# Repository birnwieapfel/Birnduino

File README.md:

# birnduino
An Arduino clone with an RS232 serial interface.

In 2013, I bought a board call "Freeduino Serial v2.0", which is an Arduino clone having an RS232 serial interface using a MAX232. But it seems that it is not available anymore now and I could not find the original files of the "v2.0". So I decided to create my own based on some information about the Freeduino I found in the internet and having a look at my "Freeduino Serial v2.0" board...

## Repository content
- The [inputs folder](inputs) contains the resources which helped me to create the schematic and PCB
- The [datasheets folder](datasheets) contains the datasheets for the used ICs
- The KiCad 6.0 files for the schematic and PCB are in the [KiCad subfolder](KiCad)
- *to come...* Image(s) of the PCB can be found in the folder *images*

## Old resouces
Here are some links which helped to realize this project:
- https://thdarduino.blogspot.com/2015/12/freeduino-serial-v20-bausatz.html

## Other links
- https://freeduino.org/freeduino_open_designs-html
- https://github.com/WestfW/Freeduino-historical

## License
Copyright 2022, Robert Birn. All Rights Reserved.

"birnduino" is licensed under [CC BY-SA 4.0](https://creativecommons.org/licenses/by-sa/4.0/legalcode) by Robert Birn.

This work, "birnduino", is a derivative of "Freeduino Serial" by CircuitJoy and Spiffed, released under CC BY-SA 2.5. 

"Freeduino Serial" is based on the Arduino Diecimila reference design (www.arduino.cc/main/ArduinoBoardDiecimila).

I started the work by using the **Arduino KiCad Library**, available here: https://github.com/Alarm-Siren/arduino-kicad-library. Remark: After an update, no reference to this library is existing anymore.

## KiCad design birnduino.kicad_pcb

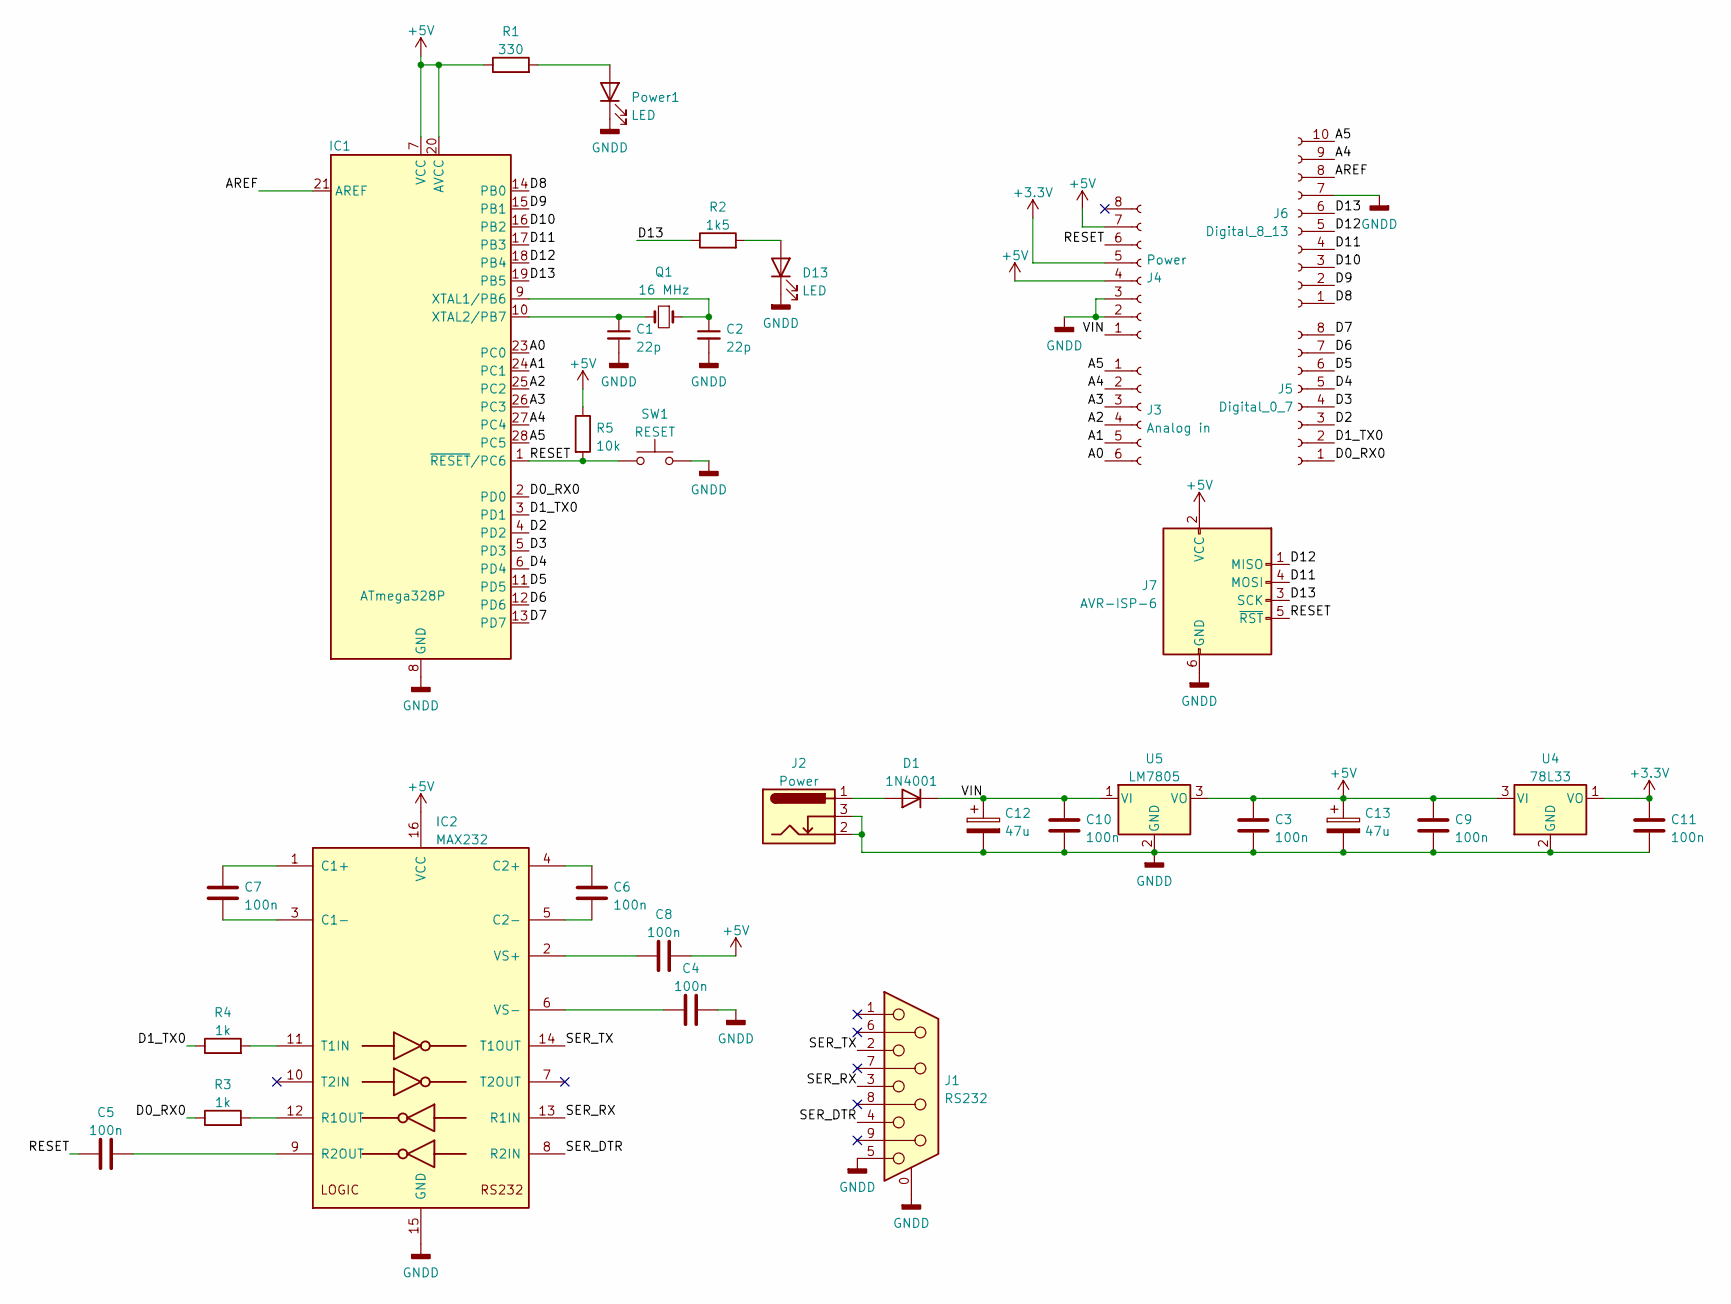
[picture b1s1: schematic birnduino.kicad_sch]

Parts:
C1, C2: 22p; C_Rect_L7.0mm_W2.0mm_P5.00mm
C3, C4, C5, C6, C7, C8, C9, C10, C11: 100n; C_Rect_L7.0mm_W2.0mm_P5.00mm
C12, C13: 47u; CP_Radial_D6.3mm_P2.50mm
D1: 1N4001; D_DO-41_SOD81_P10.16mm_Horizontal
D13: LED; LED_D3.0mm
IC1: ATmega328P; DIP-28_W7.62mm
IC2: MAX232; DIP-16_W7.62mm
J1: RS232; DSUB-9_Female_Horizontal_P2.77x2.84mm_EdgePinOffset7.70mm_H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
J2: Power; BarrelJack_Horizontal
J3: Analog in; PinSocket_1x06_P2.54mm_Vertical
J4: Power; PinSocket_1x08_P2.54mm_Vertical
J5: Digital_0_7; PinSocket_1x08_P2.54mm_Vertical
J6: Digital_8_13; PinSocket_1x10_P2.54mm_Vertical
J7: AVR-ISP-6; PinHeader_2x03_P2.54mm_Vertical
Power1: LED; LED_D3.0mm
Q1: 16 MHz; Crystal_HC49-U_Vertical
R1: 330; R_Axial_DIN0207_L6.3mm_D2.5mm_P10.16mm_Horizontal
R2: 1k5; R_Axial_DIN0207_L6.3mm_D2.5mm_P10.16mm_Horizontal
R3, R4: 1k; R_Axial_DIN0207_L6.3mm_D2.5mm_P10.16mm_Horizontal
R5: 10k; R_Axial_DIN0207_L6.3mm_D2.5mm_P10.16mm_Horizontal
SW1: RESET; SW_PUSH_6mm
U4: 78L33; TO-92_Inline
U5: LM7805; TO-220-3_Vertical

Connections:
+3V3: C11.1, J4.5, U4.1 (VO)
+5V: C3.1, C8.1, C9.1, C13.1, IC1.7 (VCC), IC1.20 (AVCC), IC2.16 (VCC), J4.4, J4.7, J7.2 (VCC), R1.1, R5.1, U4.3 (VI), U5.3 (VO)
/A0: IC1.23 (PC0), J3.6
/A1: IC1.24 (PC1), J3.5
/A2: IC1.25 (PC2), J3.4
/A3: IC1.26 (PC3), J3.3
/A4: IC1.27 (PC4), J3.2, J6.9
/A5: IC1.28 (PC5), J3.1, J6.10
/AREF: IC1.21 (AREF), J6.8
/D0_RX0: IC1.2 (PD0), J5.1, R3.1
/D1_TX0: IC1.3 (PD1), J5.2, R4.1
/D2: IC1.4 (PD2), J5.3
/D3: IC1.5 (PD3), J5.4
/D4: IC1.6 (PD4), J5.5
/D5: IC1.11 (PD5), J5.6
/D6: IC1.12 (PD6), J5.7
/D7: IC1.13 (PD7), J5.8
/D8: IC1.14 (PB0), J6.1
/D9: IC1.15 (PB1), J6.2
/D10: IC1.16 (PB2), J6.3
/D11: IC1.17 (PB3), J6.4, J7.4 (MOSI)
/D12: IC1.18 (PB4), J6.5, J7.1 (MISO)
/D13: IC1.19 (PB5), J6.6, J7.3 (SCK), R2.1
/RESET: C5.2, IC1.1 (~RESET/PC6), J4.6, J7.5 (~RST), R5.2, SW1.1
/SER_DTR: IC2.8 (R2IN), J1.4
/SER_RX: IC2.13 (R1IN), J1.3
/SER_TX: IC2.14 (T1OUT), J1.2
/VIN: C10.1, C12.1, D1.1 (K), J4.1, U5.1 (VI)
GNDD: C1.2, C2.2, C3.2, C4.2, C9.2, C10.2, C11.2, C12.2, C13.2, D13.1 (K), IC1.8 (GND), IC1.22 (GND), IC2.15 (GND), J1.0 (PAD), J1.5, J2.2, J2.3, J4.2, J4.3, J6.7, J7.6 (GND), Power1.1 (K), SW1.2, U4.2 (GND), U5.2 (GND)
unnamed: C1.1, IC1.10 (XTAL2/PB7), Q1.2
unnamed: C2.1, IC1.9 (XTAL1/PB6), Q1.1
unnamed: C4.1, IC2.6 (VS-)
unnamed: C5.1, IC2.9 (R2OUT)
unnamed: C6.1, IC2.4 (C2+)
unnamed: C6.2, IC2.5 (C2-)
unnamed: C7.1, IC2.1 (C1+)
unnamed: C7.2, IC2.3 (C1-)
unnamed: C8.2, IC2.2 (VS+)
unnamed: D1.2 (A), J2.1
unnamed: D13.2 (A), R2.2
unnamed: IC2.11 (T1IN), R4.2
unnamed: IC2.12 (R1OUT), R3.2
unnamed: Power1.2 (A), R1.2

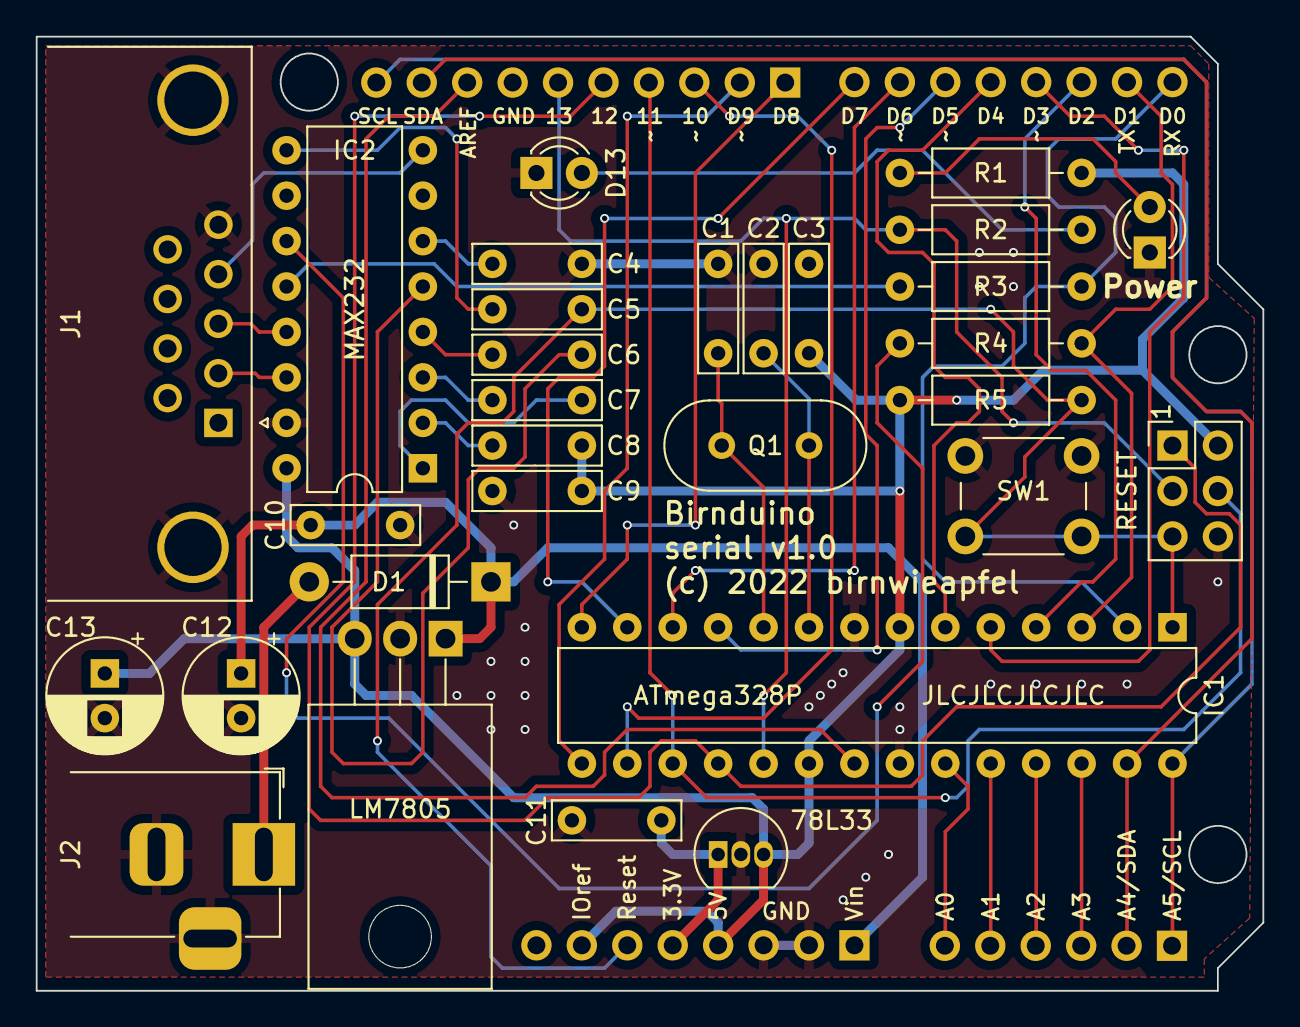
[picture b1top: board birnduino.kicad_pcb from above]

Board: 2 copper layers, 68.6 x 53.3 mm, 34 parts (0 on the bottom side), 43 nets.

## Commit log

2022-11-01 Fixed some issues detected by ERC. No impact on board layout.
2022-11-01 Update of board/library to change D-SUB connector and power jack.
2022-11-01 Removed dependencies to Arduino KiCad Library
2022-11-01 Removed Arduino KiCad Library
2022-11-01 Update of gerber files
2022-11-01 Removed J1 and J2 labels
2022-11-02 Restructured repository and added additional files

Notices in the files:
birnduino.kicad_pcb:
(c) 2022 birnwieapfel
